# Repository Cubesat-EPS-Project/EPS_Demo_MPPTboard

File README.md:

# EPS_Demo_MPPTboard
 Demo pcb board for MPPT

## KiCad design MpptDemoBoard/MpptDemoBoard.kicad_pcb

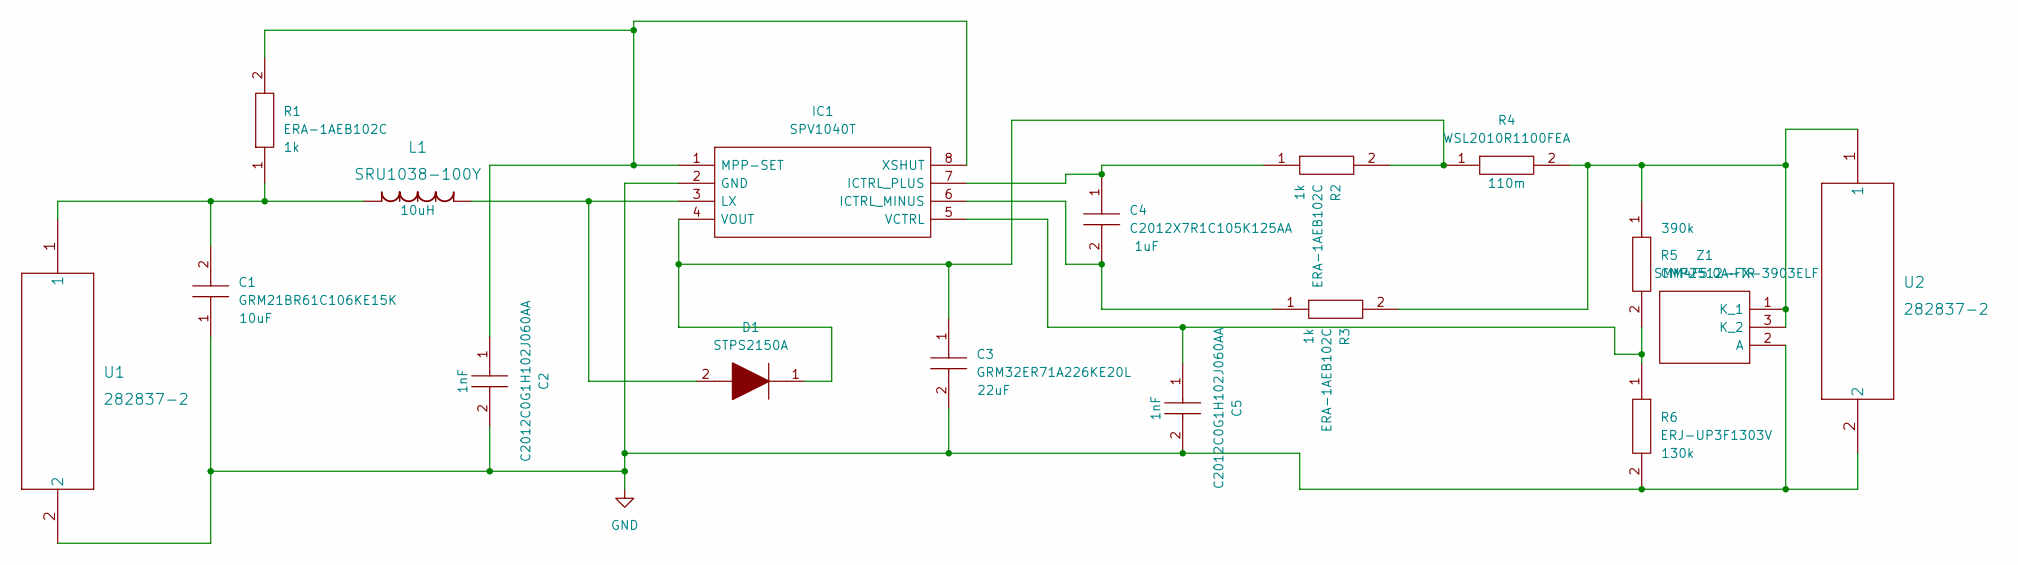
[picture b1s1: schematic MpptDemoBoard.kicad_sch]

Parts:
C1: GRM21BR61C106KE15K; Mouser Part Number 81-GRM21BR61C106KE5K
C2, C5: C2012C0G1H102J060AA; Mouser Part Number 810-C2012C0G1H102J
C3: GRM32ER71A226KE20L; Mouser Part Number 81-GRM32R71A226KE20L
C4: C2012X7R1C105K125AA; Mouser Part Number 810-C2012X7R1C105K-3
D1: STPS2150A; Mouser Part Number 511-STPS2150A
IC1: SPV1040T; Mouser Part Number 511-SPV1040T
L1: SRU1038-100Y
R1, R2, R3: ERA-1AEB102C; Mouser Part Number 667-ERA-1AEB102C
R4: WSL2010R1100FEA; Mouser Part Number 71-WSL2010R1100FEA
R5: CMP2512-FX-3903ELF; Mouser Part Number 652-CMP2512-FX-3903L
R6: ERJ-UP3F1303V; Mouser Part Number 667-ERJ-UP3F1303V
U1, U2: 282837-2
Z1: SMM4F5.0A-TR; Mouser Part Number 511-SMM4F5.0A-TR

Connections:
GND: C1.1, C2.2, C3.2, C5.2, IC1.2 (GND), R6.2, U1.2, U2.2, Z1.2 (A)
unnamed: C1.2, L1.2, R1.1, U1.1
unnamed: C2.1, IC1.1 (MPP-SET), IC1.8 (XSHUT), R1.2
unnamed: C3.1, D1.1, IC1.4 (VOUT), R2.2, R4.1
unnamed: C4.1, IC1.7 (ICTRL_PLUS), R2.1
unnamed: C4.2, IC1.6 (ICTRL_MINUS), R3.1
unnamed: C5.1, IC1.5 (VCTRL), R5.2, R6.1
unnamed: D1.2, IC1.3 (LX), L1.1
unnamed: R3.2, R4.2, R5.1, U2.1, Z1.1 (K_1), Z1.3 (K_2)

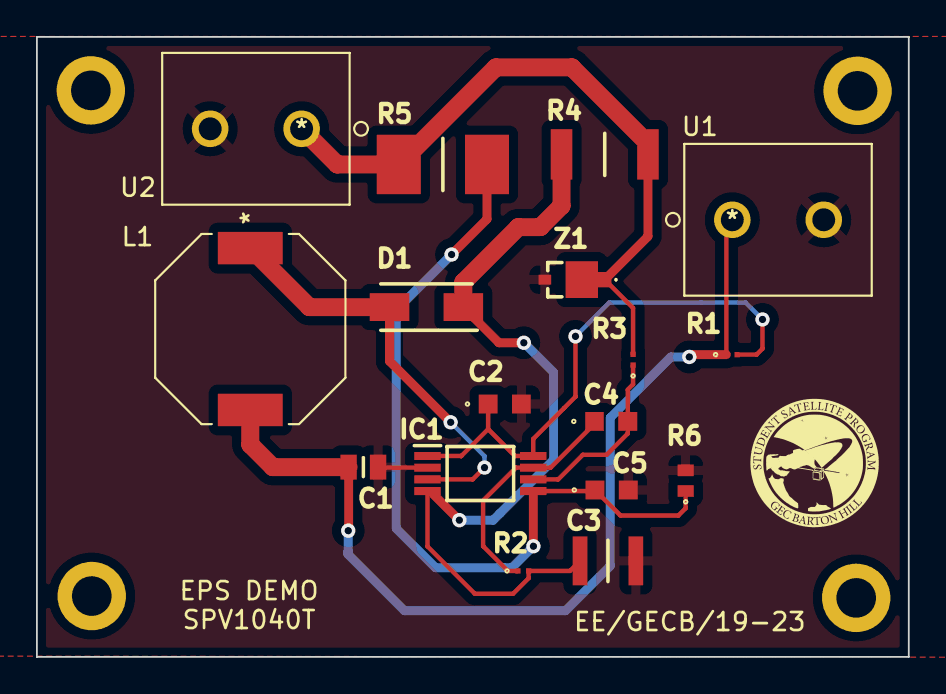
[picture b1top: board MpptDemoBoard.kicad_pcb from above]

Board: 2 copper layers, 48.4 x 34.4 mm, 17 parts (0 on the bottom side), 9 nets.

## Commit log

2023-02-04 Mppt PCB
    Demo pcb board for implementing MPPT using SPV1040T IC.
2023-02-10 Updated PCB
    Added corner chamfer
2023-02-10 Updated pcb with new diode
    replaced diode STPS120MF (If=1A) with STPS2150A (If=2A). Updated symbol and footprint library and docs containing schematic, pcb layout image and 3d image.
2023-02-13 Updated BOM
    BOM updated with diode stps2150a
2023-02-13 Added gerber folder
    added gerber folder containing gerber, drill files and BOM

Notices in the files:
parts and their libraries:
Copyright 2021 Accelerated Designs. All rights reserved.
